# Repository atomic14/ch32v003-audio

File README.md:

# CH32V003J4M6 Audio Projects

A collection of audio projects for the CH32V003J4M6 RISC-V microcontroller, demonstrating various audio synthesis and playback techniques on an 8-pin, $0.10 microcontroller. From simple 1-bit music to compressed audio sample playback and speech synthesis. Click on the image to watch a video and hear the results.

## Project Overview

This repository contains several firmware projects and development tools:

### Firmware Projects

1. **SimpleSoundFirmware** - Single-voice 1-bit music playback (monophonic)
2. **PolyphonicSoundFirmware** - Advanced 8-voice polyphonic music with PWM synthesis
3. **SamplePlayback** - Compressed audio sample playback (IMA ADPCM, QOA, 2-bit ADPCM)
4. **Talkie** - Speech synthesis using the Talkie library

### Development Tools

5. **Buzzer Studio** - Interactive web app for designing 1-bit sound effects and exporting MIDI tracks

The **Buzzer Studio** project is available here: https://buzzer-studio.atomic14.com/

A word of warning - the **Buzzer Studio** codebase was creating with a lot of help from AI tools. It all runs client side, there is no backend for anyone to hack. But the code may not always be easy for a human to understand.

## Quick Start

### Building the Firmware

All firmware projects build with PlatformIO. To build locally:

**Simple Sound Firmware (1-bit monophonic):**
```bash
cd SimpleSoundFirmware
pio run
```

**Polyphonic Sound Firmware (8-voice PWM):**
```bash
cd PolyphonicSoundFirmware
pio run
```

**Sample Playback (compressed audio):**
```bash
cd SamplePlayback
pio run
```

**Talkie (speech synthesis):**
```bash
cd Talkie
pio run
```

For detailed firmware information, see each project's README:
- [SimpleSoundFirmware/README.md](SimpleSoundFirmware/README.md) - Original single-voice 1-bit music
- [PolyphonicSoundFirmware/README.md](PolyphonicSoundFirmware/README.md) - 8-voice polyphonic synthesis
- [SamplePlayback/README.md](SamplePlayback/README.md) - Compressed audio playback with multiple codecs
- [Talkie/README.md](Talkie/README.md) - Speech synthesis implementation

### Converting Music Files and Creating Sound Effects

**Buzzer Studio (Web App):**
```bash
cd buzzer-studio
npm install
npm run dev
```

The app allows you to:
- Export tracks from MIDI files for 1-bit playback
- Design sound effects with real-time preview
- Export to C arrays for microcontrollers
- Export to Python for MicroPython/CircuitPython
- Choose from preset effects (jump, coin, laser, etc.)
- Play LPC encoded audio
- Encode WAV files to LPC

## Hardware Requirements

- **Microcontroller**: CH32V003J4M6 (RISC-V, 8-pin SOIC)
- **Power**: 3.3V supply
- **Programming**: WCH-Link or compatible programmer

### Pin Configurations

**SimpleSoundFirmware (1-bit music):**
- **Output**: Piezo buzzer or small speaker (connected to PD6)
- **Input**: Trigger button or signal (connected to PC1)

**PolyphonicSoundFirmware (8-voice music):**
- **Output**: Piezo buzzer or small speaker (connected to PA1)
- **No trigger input**: Plays automatically on startup

**SamplePlayback (compressed audio):**
- **Output**: PWM audio output on PA1 (8-bit via PWM)
- **No trigger input**: Plays automatically on startup

**Talkie (speech synthesis):**
- **Output**: PWM audio output on PA1 (8-bit via PWM)
- **No trigger input**: Plays speech on startup

## Project Structure

```
brain-transplant/
├── SimpleSoundFirmware/      # 1-bit monophonic music playback
│   ├── src/                  # Source code (main.cpp, music data)
│   ├── platformio.ini        # Build configuration
│   └── README.md             # Documentation
│
├── PolyphonicSoundFirmware/  # 8-voice polyphonic music
│   ├── src/                  # Source code (polyphonic player)
│   ├── platformio.ini        # Build configuration
│   └── README.md             # Documentation
│
├── SamplePlayback/           # Compressed audio sample playback
│   ├── src/                  # Source code (ADPCM decoders, PWM player)
│   │   ├── AudioStream.h     # Base interface for codecs
│   │   ├── IMAAdpcmStream.*  # IMA ADPCM decoder
│   │   ├── ADPCM2BitStream.* # 2-bit ADPCM decoder
│   │   ├── player.*          # PWM playback engine
│   │   └── audio/            # Audio data files
│   ├── platformio.ini        # Build configuration
│   └── README.md             # Documentation
│
├── Talkie/                   # Speech synthesis
│   ├── src/                  # Source code (Talkie library port)
│   │   ├── Talkie.*          # Speech synthesis engine
│   │   ├── phrases.*         # Pre-defined speech phrases
│   │   └── player.*          # Audio playback
│   ├── platformio.ini        # Build configuration
│   └── README.md             # Documentation
│
├── scripts/                  # Python audio conversion tools
│   ├── wav_to_adpcm_c.py     # WAV → ADPCM C array converter
│   ├── adpcm_2bit_decoder.py # 2-bit ADPCM decoder
│   ├── compare_audio.py      # Audio comparison tools
│   ├── pyproject.toml        # Python dependencies (uv)
│   └── README.md             # Scripts documentation
│
├── buzzer-studio/            # Interactive web app
│   ├── src/                  # TypeScript source code
│   ├── public/               # Static assets
│   ├── index.html            # App entry point
│   ├── package.json          # Dependencies and scripts
│   └── README.md             # App documentation
│
└── .github/
    └── workflows/
        ├── build-firmware.yml      # Firmware CI/CD
        └── buzzer-studio-ci.yml    # Buzzer Studio CI/CD
```

## Documentation

### Firmware Projects
- **[SimpleSoundFirmware](SimpleSoundFirmware/README.md)** - 1-bit monophonic music playback
- **[PolyphonicSoundFirmware](PolyphonicSoundFirmware/README.md)** - 8-voice polyphonic synthesis
- **[SamplePlayback](SamplePlayback/README.md)** - Compressed audio playback with multiple codec support
- **[Talkie](Talkie/README.md)** - Speech synthesis implementation

### Development Tools
- **[Buzzer Studio](buzzer-studio/)** - Web app for designing 1-bit sound effects and exporting MIDI
- **[Scripts](scripts/README.md)** - Python tools for audio conversion and ADPCM encoding

## Development

### Prerequisites

**For Firmware Development:**
- [PlatformIO](https://platformio.org/) - Embedded build system
- CH32V platform support (installed automatically by PlatformIO)
- WCH-Link programmer (or compatible)

**For Buzzer Studio App:**
- Node.js 18+ and npm
- Modern web browser with Web Audio API support

**For Python Scripts:**
- Python 3.8+
- [uv](https://github.com/astral-sh/uv) package manager

## How It Works

### Firmware Approaches

**SimpleSoundFirmware (1-bit music):**
1. Waits for trigger signal on pin PC1
2. Toggles output pin (PD6) at specified frequencies
3. Uses microsecond-precision delays for accurate timing
4. Simple 1-bit audio (square wave)

**PolyphonicSoundFirmware (8-voice music):**
1. Automatically starts on power-up
2. Manages up to 8 simultaneous voices using PWM synthesis
3. Outputs mixed audio through PA1 at 8 kHz sample rate
4. Software mixing with real-time voice generation

**SamplePlayback (compressed audio):**
1. Decodes compressed audio using codec decoders (IMA ADPCM, 2-bit ADPCM)
2. Outputs 8-bit audio via PWM on PA1 at 8 kHz
3. Supports multiple codec formats with extensible architecture
4. Compression ratios of 2:1 and 4:1

**Talkie (speech synthesis):**
1. Uses Linear Predictive Coding (LPC) for speech synthesis
2. Pre-defined vocabulary of phonemes and words
3. Outputs synthesized speech via PWM on PA1
4. Real-time speech generation from phrase data

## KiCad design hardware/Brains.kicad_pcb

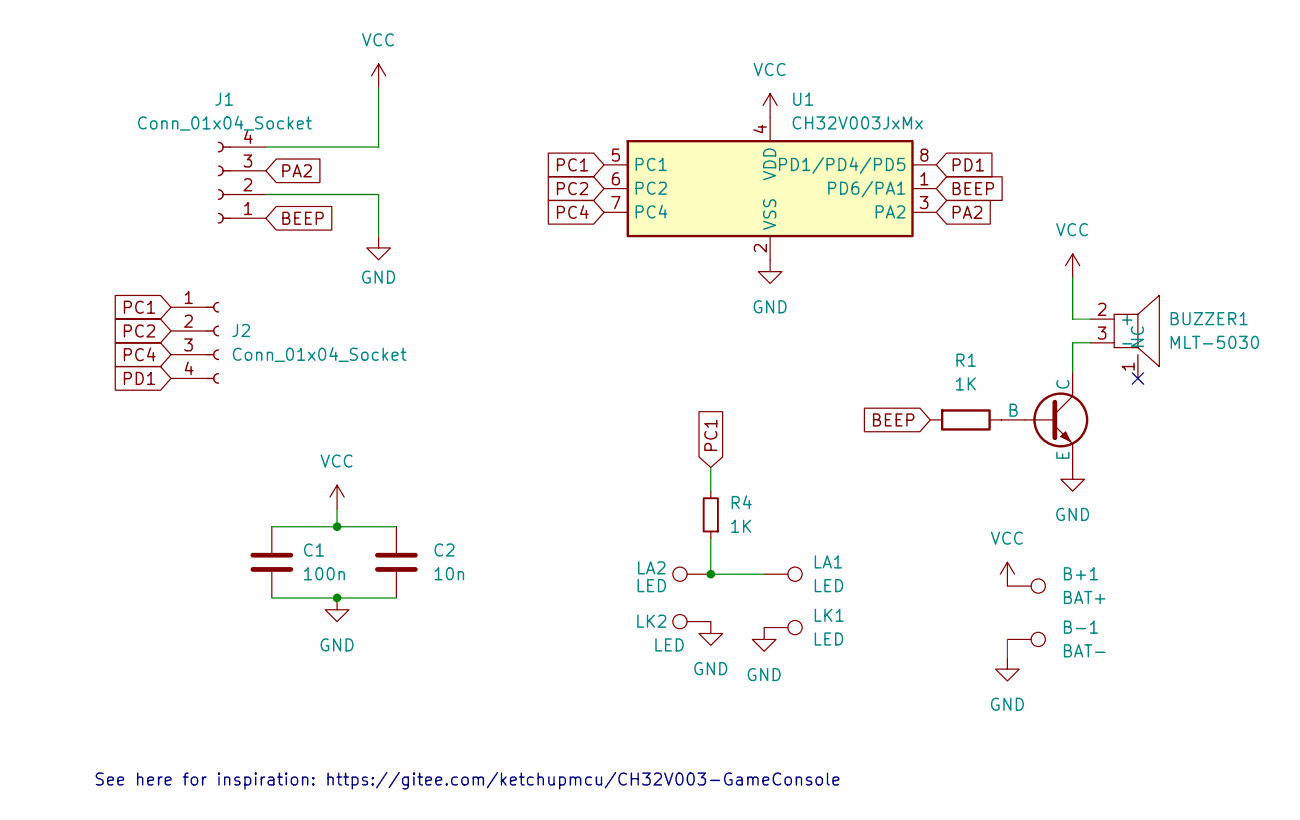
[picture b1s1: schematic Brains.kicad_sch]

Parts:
B+1: BAT+; TestPoint_Pad_1.5x1.5mm
B-1: BAT-; TestPoint_Pad_1.5x1.5mm
BUZZER1: MLT-5030; BUZ-SMD_3P-L5.2-W5.2-P3.50-BR; LCSC Part C95297
C1: 100n; C_0603_1608Metric
C2: 10n; C_0603_1608Metric
J1, J2: Conn_01x04_Socket; PinHeader_1x04_P2.54mm_Vertical
LA1, LA2: LED; TestPoint_Pad_1.5x1.5mm
LK1, LK2: LED; TestPoint_Pad_1.5x1.5mm
Q2: MMBT2222A; SOT-23
R1, R4: 1K; R_0603_1608Metric
U1: CH32V003JxMx; JEITA_SOIC-8_3.9x4.9mm_P1.27mm

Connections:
BEEP: J1.1, R1.2, U1.1 (PD6/PA1)
GND: B-1.1, C1.2, C2.2, J1.2, LK1.1, LK2.1, Q2.2 (E), U1.2 (VSS)
unnamed: BUZZER1.3 (-), Q2.3 (C)
unnamed: LA1.1, LA2.1, R4.1
unnamed: Q2.1 (B), R1.1
PA2: J1.3, U1.3 (PA2)
PC1: J2.1, R4.2, U1.5 (PC1)
PC2: J2.2, U1.6 (PC2)
PC4: J2.3, U1.7 (PC4)
PD1: J2.4, U1.8 (PD1/PD4/PD5)
VCC: B+1.1, BUZZER1.2 (+), C1.1, C2.1, J1.4, U1.4 (VDD)

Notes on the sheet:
See here for inspiration: https://gitee.com/ketchupmcu/CH32V003-GameConsole

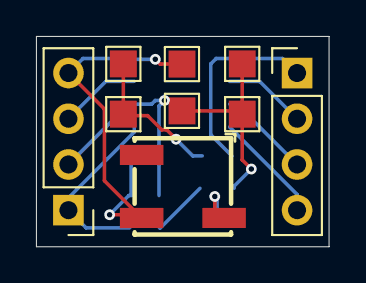
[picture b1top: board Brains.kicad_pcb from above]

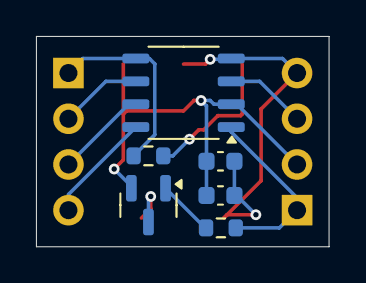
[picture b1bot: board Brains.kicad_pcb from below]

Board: 2 copper layers, 16.3 x 11.7 mm, 15 parts (6 on the bottom side), 11 nets.

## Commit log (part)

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2025-10-05 readme file
2025-10-05 Goes into sleep mode
2025-10-05 github action to check firmware
2025-10-05 Adds badge
2025-10-05 Install the package
2025-10-06 Adds simple 1bit sound effects
2025-10-06 Adds github actions for sound_effects project
2025-10-06 Adds badge to readme
2025-10-06 midi note extractor
2025-10-06 Improve visualisation
2025-10-07 Adds instructions
2025-10-07 Go into deep sleep
2025-10-08 Code cleanup
2025-10-10 WIP polyphonic sound
2025-10-10 Fix naming
2025-10-10 Update readme file
2025-10-10 Fix case
2025-10-10 Create LICENSE
2025-10-10 Simplifies things by using rests instead of delays
2025-10-10 Removes delay_us completely
2025-10-11 Adds ci for midi-extactor
2025-10-11 Fix ci for midi extractor
2025-10-11 Fix workflow name
2025-10-11 combine tools into one
2025-10-11 Favicons
2025-10-11 remove video transcript
2025-10-11 Clean up README
2025-10-11 Remove extraneous file
2025-10-12 Refine project description in README.md
    Updated project description for clarity and conciseness.
2025-10-12 Enhance README with video link for project demo
    Added a call to action to watch a video demonstration of the project.
2025-10-13 Fixes polyphonic player
2025-10-13 Make our track splitting less agreesive
2025-10-17 Adds hardware
2025-10-24 talkie code cleanup
2025-10-26 new spelling
2025-10-26 Adds talkie playback
2025-10-26 LPC encoder
2025-10-26 Name tabs correctly
2025-10-26 Add Arnie phrase to Talkie
2025-10-26 Point to the buzzer studio online deployment
2025-10-26 Fixes linting errors
2025-10-26 fix build error on polyphonic player
2025-10-26 Adds adpcm converter to toolbox
2025-10-26 Fix styling of success etc...
2025-10-27 Move out redudant scripts - these are all done by the buzzer_studio now.
2025-10-27 Rename file to match class
2025-10-27 Make playback code even smaller.
2025-10-27 Improve youtube links
2025-10-29 New YT thumb
2025-10-31 Improve LPC encoding
2025-10-31 Fix linter errors and make pre-processing default to off.
2025-11-03 Major refactor of LPC endoding.
2025-11-03 svelte-port
2025-11-04 Adds lots of new phrases
2025-11-04 Adds a stop button
2025-11-04 Pre-processing tweaks
2025-11-04 Improve debug UI
2025-11-04 fix build
2025-11-06 Adds TMS52200 variant
2025-11-07 Adds a low pass filter on the output of talkiestream and interpolates the params
2025-11-07 Resets intepolation properly
2025-11-07 HAndle stop frame interpolation
2025-11-11 Improve UI and code cleanup
2025-11-11 Adds setting for silence
2025-11-12 Adds alternrative voice detection
2025-11-15 Adds routing
2025-11-15 change routing to paths
2025-11-16 Adds LPC explanation
2025-11-16 fixes linting
2025-11-16 Add pre-commit hooks for CI checks
2025-11-16 Add node_modules to root .gitignore
2025-11-16 Adds google analytics
2025-11-20 Adds spectrogram and tweaks UI
2025-11-20 Refector and clean up
2025-11-20 Tweak style
2025-11-20 Adds video embed
